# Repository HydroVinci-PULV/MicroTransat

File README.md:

# Architecture
Ceci est une ébauche de l'architecture finale des systèmes embarqués du bateau.

Cette présentation de l'architecture est amenée à évoluer en fonction des besoins du projet.

> **Note :** Les protocoles de communications entre les différents composants ne sont pas représentatifs de la réalité puisque le choix des composants n'est pas définitif à ce stade.

# Composants

## Ordinateur de bord

<p>Considérant que notre bateau autonomme puisse être apparenté à un drone, nous avons fait le choix d'utiliser un <i>flight controller</i> comme ordinateur de bord. C'est pourquoi nous utilisons au sein de notre architecture de navigation un <i>BeagleBone Blue</i> choisit pour sa compatibilité avec .</p>

Vous trouverez plus d'information sur le *BeagleBone Blue* sur [la page dédiée](../../wiki/BeagleBone-Blue) dans le wiki du projet.

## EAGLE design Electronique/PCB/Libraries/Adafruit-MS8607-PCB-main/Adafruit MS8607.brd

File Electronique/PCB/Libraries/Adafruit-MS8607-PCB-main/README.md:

## Adafruit MS8607 PTH Sensor PCB

<a href="http://www.adafruit.com/products/4716"><br/>
Click here to purchase one from the Adafruit shop</a>

PCB files for the Adafruit MS8607 PTH Sensor. 

Format is EagleCAD schematic and board layout
* https://www.adafruit.com/product/4716

### Description

Because of their many applications, Pressure, Temperature, and Humidity sensors (PHT sensors) are a common offering from semiconductor companies. The MS8607 PHT sensor from TE Connectivity  does an admirable job of measuring a wide range of all three environmental conditions. Each and every MS8607 sensor is calibrated at the factory and the calibration constants stored in the sensor itself. This sensor is a one stop shop for all your common weather and environmental related metrics. Just add a MS8607 and you’ll be ready to finish your enclosure and retire as a [Dubia Cockroach Farmer](https://dubiaroachdepot.com/guidance/breeding-dubia-roaches#thermometer)

The MS8607 provides the previously mentioned factory-calibrated pressure, temperature, and humidity data are recorded as **16-bit** values and made available over an I2C bus for simple, two wire (plus power and ground!) connection to your microcontroller. Pressure measurements accuracy comes in at **+/- 2 hPa**, relative humidity at **+/- 3% rH**, and temperature is good to within 1 degree Celsius. One standout feature of the MS8607 is it’s very respectable low power consumption at **as low as 0.78 µA** ! That’s hardly anything! Along with carefully managed microcontroller power usage, getting good battery life out of your sensing project will be that much easier.

### License

Adafruit invests time and resources providing this open source design, please support Adafruit and open-source hardware by purchasing products from [Adafruit](https://www.adafruit.com)!

Designed by Bryan Siepert for Adafruit Industries.

Creative Commons Attribution/Share-Alike, all text above must be included in any redistribution. 
See license.txt for additional details.

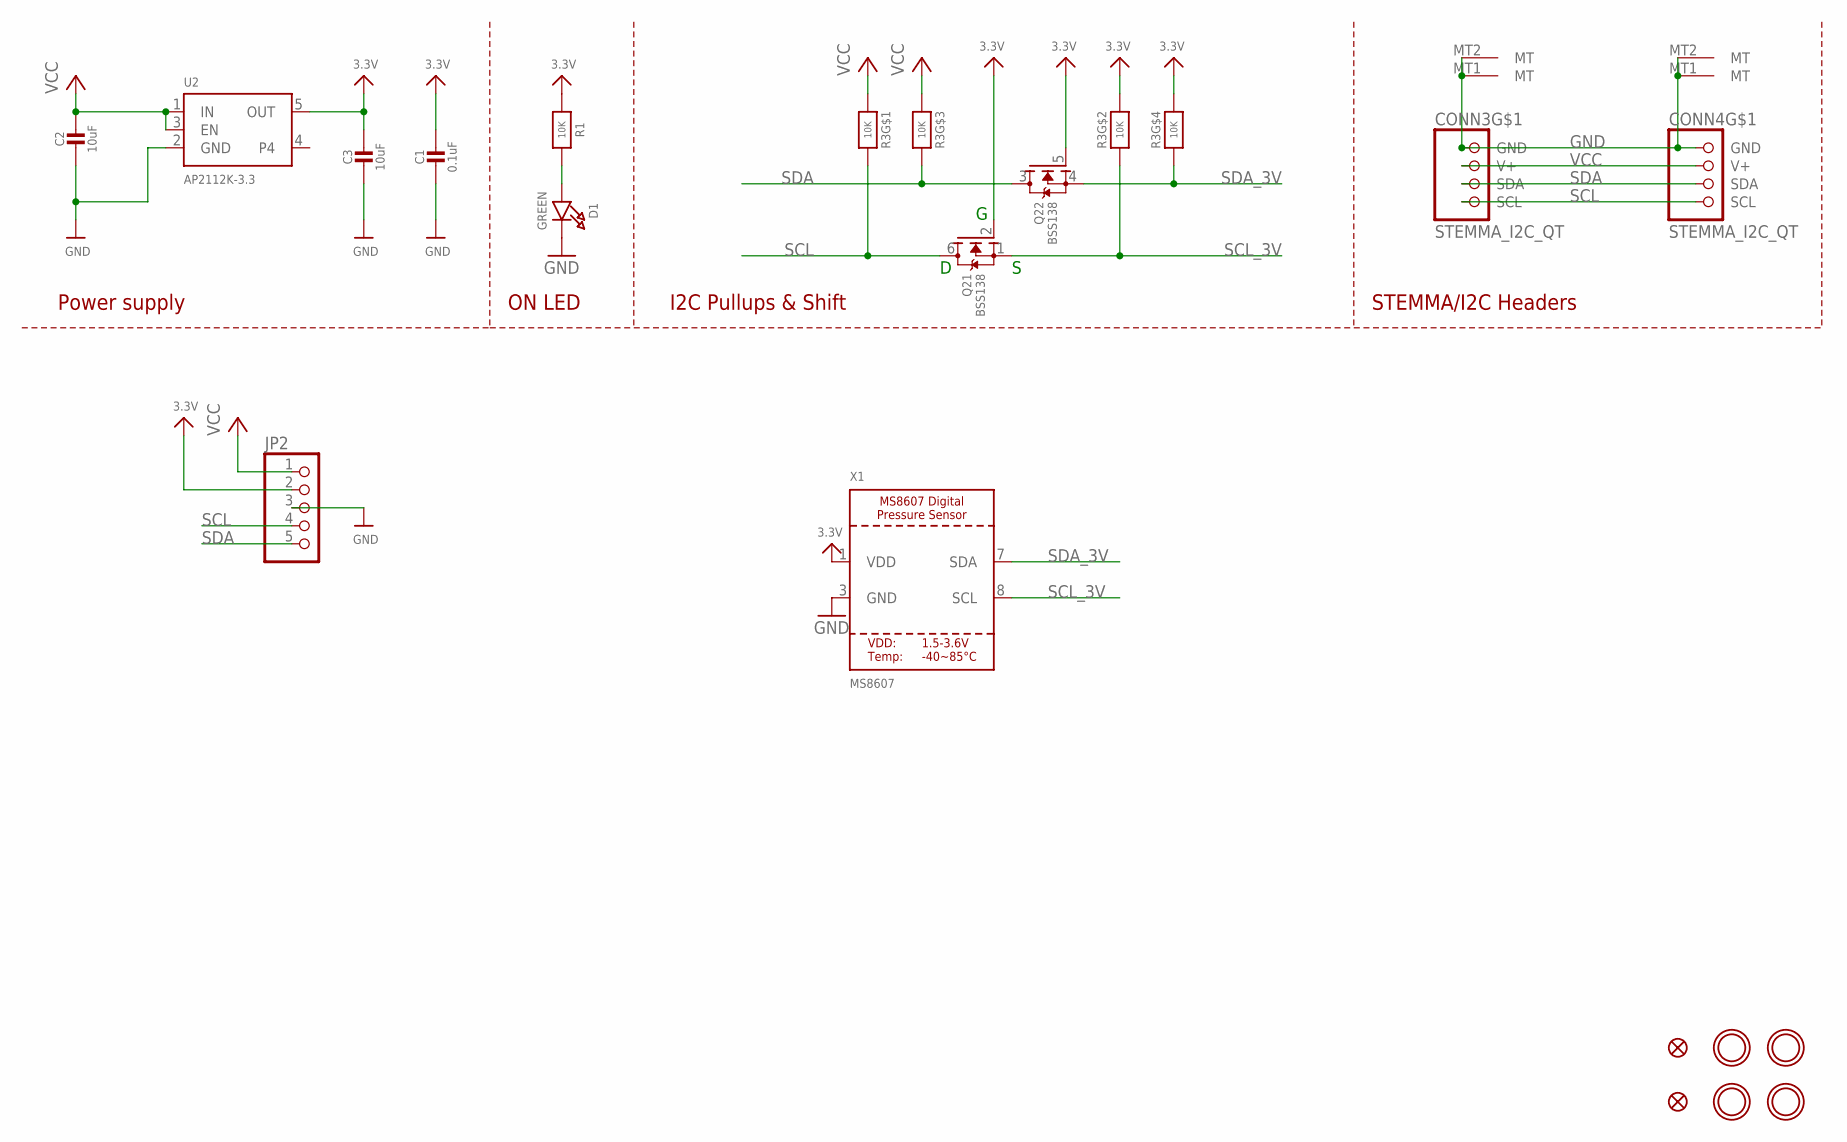
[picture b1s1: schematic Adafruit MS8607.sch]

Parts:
C1: 0.1uF; 0603-NO
C2, C3: 10uF; 0805-NO
CONN3, CONN4: STEMMA_I2C_QT; JST_SH4
D1: GREEN; CHIPLED_0603_NOOUTLINE
FID3, FID4: FIDUCIAL_1MM
JP2: HEADER-1X5ROUND; 1X05_ROUND
Q2: BSS138; SOT363
R1: 10K; 0603-NO
R3: 10K; RESPACK_4X0603
U2: AP2112K-3.3; SOT23-5
U$1, U$17, U$19, U$21: MOUNTINGHOLE2.5; MOUNTINGHOLE_2.5_PLATED
X1: MS8607

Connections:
3.3V: C1.1, C3.1, JP2.2, Q2.2 (G), Q2.5 (G), R1.1, R3.2 (1), R3.4 (1), U2.5 (OUT), X1.1 (VDD)
GND: C1.2, C2.2, C3.2, CONN3.1 (GND), CONN3.MT1 (MT), CONN3.MT2 (MT), CONN4.1 (GND), CONN4.MT1 (MT), CONN4.MT2 (MT), D1.C, JP2.3, U2.2 (GND), X1.3 (GND)
unnamed: D1.A, R1.2
SCL: CONN3.4 (SCL), CONN4.4 (SCL), JP2.4, Q2.6 (D), R3.8 (2)
SCL_3V: Q2.1 (S), R3.7 (2), X1.8 (SCL)
SDA: CONN3.3 (SDA), CONN4.3 (SDA), JP2.5, Q2.3 (D), R3.6 (2)
SDA_3V: Q2.4 (S), R3.5 (2), X1.7 (SDA)
VCC: C2.1, CONN3.2 (V+), CONN4.2 (V+), JP2.1, R3.1, R3.3 (1), U2.1 (IN), U2.3 (EN)

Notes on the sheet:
I2C Pullups & Shift
STEMMA/I2C Headers
ON LED
Power supply

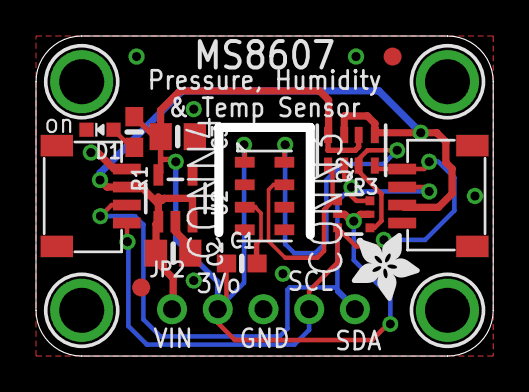
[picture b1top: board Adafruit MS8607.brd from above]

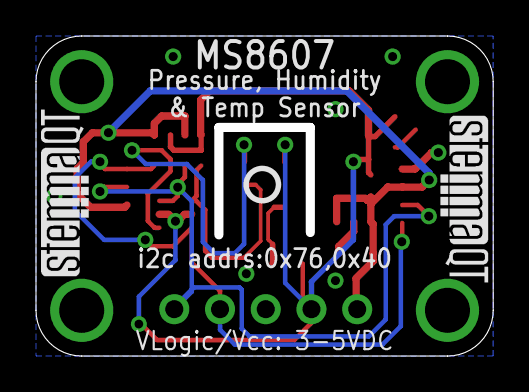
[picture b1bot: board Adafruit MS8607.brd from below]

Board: 2 copper layers, 25.4 x 17.8 mm, 22 parts (3 on the bottom side), 8 nets.

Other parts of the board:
U$22: ADAFRUIT_3.5MM
U$25: PCBFEAT-REV-040
U$30, U$31: STEMMAQT

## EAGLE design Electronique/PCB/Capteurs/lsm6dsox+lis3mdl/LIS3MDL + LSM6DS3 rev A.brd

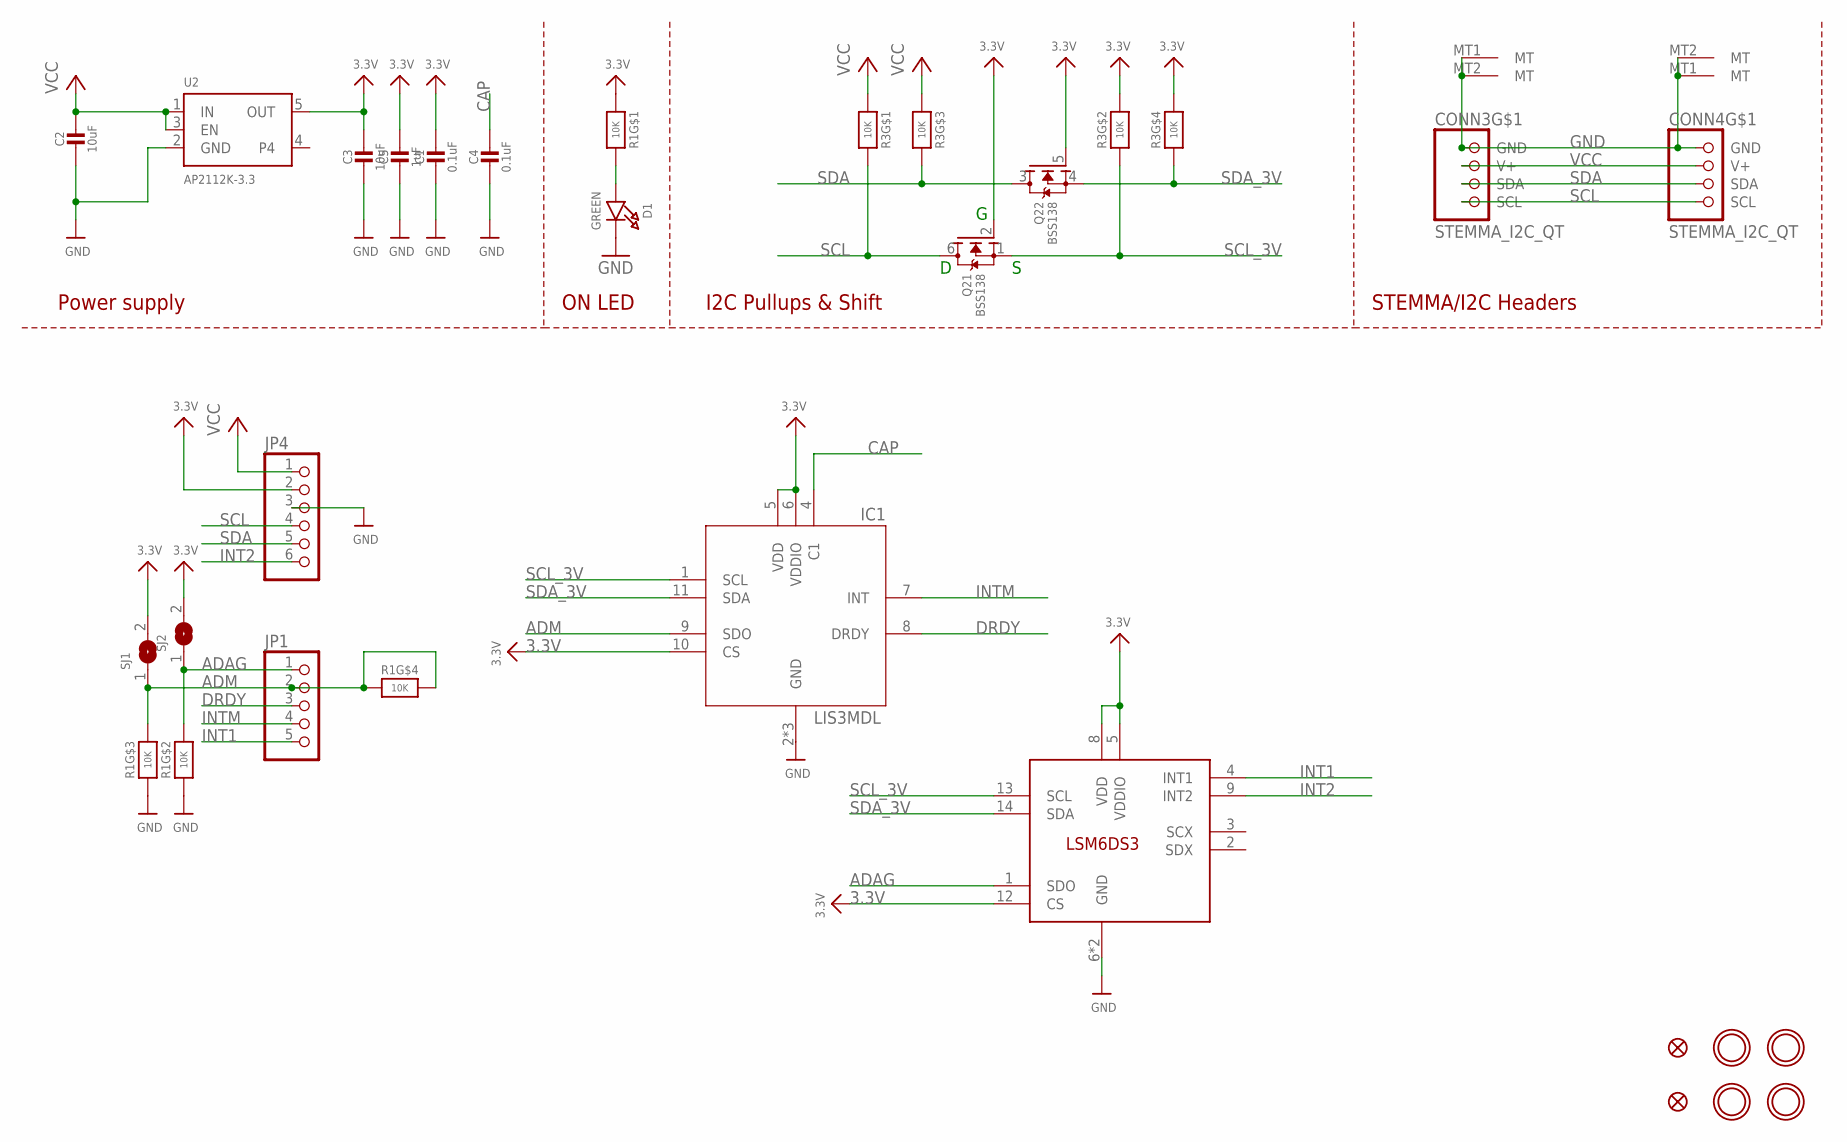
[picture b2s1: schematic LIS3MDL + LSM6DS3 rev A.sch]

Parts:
C1, C4: 0.1uF; 0603-NO
C2, C3: 10uF; 0805-NO
C5: 1uF; 0603-NO
CONN3, CONN4: STEMMA_I2C_QT; JST_SH4
D1: GREEN; CHIPLED_0603_NOOUTLINE
FID3, FID4: FIDUCIAL_1MM
IC1: LIS3MDL; LGA12_2X2MM
JP1: HEADER-1X570MIL; 1X05_ROUND_70
JP4: HEADER-1X670MIL; 1X06_ROUND_70
Q2: BSS138; SOT363
R1, R3: 10K; RESPACK_4X0603
SJ1, SJ2: SOLDERJUMPER; SOLDERJUMPER_ARROW_NOPASTE
U2: AP2112K-3.3; SOT23-5
U$1, U$17, U$19, U$21: MOUNTINGHOLE2.5; MOUNTINGHOLE_2.5_PLATED
U$36: LSM6DS3; LGA-14L

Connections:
3.3V: C1.1, C3.1, C5.1, IC1.5 (VDD), IC1.6 (VDDIO), IC1.10 (CS), JP4.2, Q2.2 (G), Q2.5 (G), R1.1, R3.2 (1), R3.4 (1), SJ1.2, SJ2.2, U2.5 (OUT), U$36.5 (VDDIO), U$36.8 (VDD), U$36.12 (CS)
ADAG: JP1.1, R1.7 (2), SJ2.1, U$36.1 (SDO)
ADM: IC1.9 (SDO), JP1.2, R1.4 (1), R1.5 (2), R1.6 (2), SJ1.1
CAP: C4.1, IC1.4 (C1)
DRDY: IC1.8 (DRDY), JP1.3
GND: C1.2, C2.2, C3.2, C4.2, C5.2, CONN3.1 (GND), CONN3.MT1 (MT), CONN3.MT2 (MT), CONN4.1 (GND), CONN4.MT1 (MT), CONN4.MT2 (MT), D1.C, IC1.2 (GND), IC1.3 (GND), IC1.12 (GND), JP4.3, R1.2 (1), R1.3 (1), U2.2 (GND), U$36.6 (GND), U$36.7 (GND)
INT1: JP1.5, U$36.4 (INT1)
INT2: JP4.6, U$36.9 (INT2)
INTM: IC1.7 (INT), JP1.4
unnamed: D1.A, R1.8 (2)
SCL: CONN3.4 (SCL), CONN4.4 (SCL), JP4.4, Q2.6 (D), R3.8 (2)
SCL_3V: IC1.1 (SCL), Q2.1 (S), R3.7 (2), U$36.13 (SCL)
SDA: CONN3.3 (SDA), CONN4.3 (SDA), JP4.5, Q2.3 (D), R3.6 (2)
SDA_3V: IC1.11 (SDA), Q2.4 (S), R3.5 (2), U$36.14 (SDA)
VCC: C2.1, CONN3.2 (V+), CONN4.2 (V+), JP4.1, R3.1, R3.3 (1), U2.1 (IN), U2.3 (EN)

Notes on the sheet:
I2C Pullups & Shift
STEMMA/I2C Headers
ON LED
Power supply

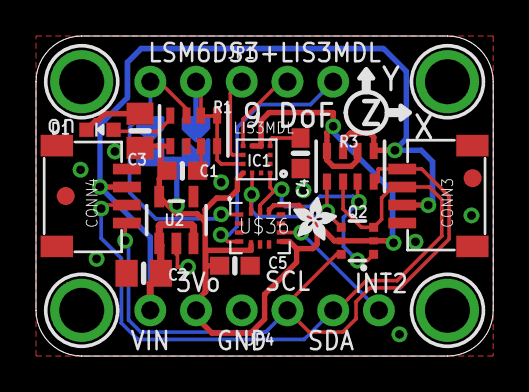
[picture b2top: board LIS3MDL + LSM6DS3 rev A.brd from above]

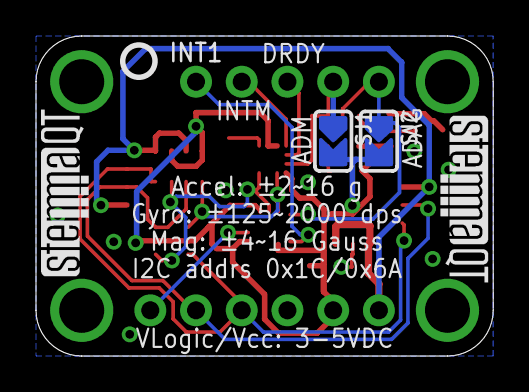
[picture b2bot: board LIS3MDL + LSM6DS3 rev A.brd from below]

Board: 2 copper layers, 25.4 x 17.8 mm, 28 parts (5 on the bottom side), 15 nets.

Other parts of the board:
U$20: ADAFRUIT_2.5MM
U$25: PCBFEAT-REV-040
U$30, U$31: STEMMAQT

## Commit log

2021-12-15 navigation algorithms research
2022-01-16 compressor
2022-01-16 Modélisations ordinateur de bord
2022-01-17 Modélisation bateau
2022-01-17 décompressor
2022-01-18 compatibilité solidworks
2022-01-18 autres modé
2022-02-04 decompress : ok pour lat
2022-02-04 data to send
2022-02-05 gps done + unit tests + explications
2022-02-05 debug instructions
2022-02-05 start boat speed compression
2022-02-05 boat speed + data concat
2022-02-05 clean
2022-02-05 updated instruction with unit test
2022-02-05 bits
2022-02-21 logos
2022-02-24 update banner
2022-03-08 Update telemetry.c
    added compression and decompression for heading
2022-04-06 Add architecture v3 to readme
2022-04-06 add paraph on flight controller
2022-04-06 fix wiki page url
2022-04-19 start rust conversion
2022-04-19 Create LICENSE
2022-04-22 j'enleve la v3
2022-04-22 mise a jour archi
2022-05-30 genetic algo for navigation
2022-06-08 bug correction in concat + added unit tests
2022-06-08 bug correction + added unit tests
2022-07-17 draft of rs485 pcb
2022-08-23 BBB pinout
2023-02-01 cad files for adafruit temp/hum/pres sensor + imu
2023-02-02 pcb files for sensors
2023-03-09 update to pcb for environnement sensors + external libs
2023-03-22 kicad schematic for ttl to rs485 conversion module
2023-03-26 ttl to rs485 proto pcb
2023-03-26 update to ttl to rs485 pcb
2023-04-01 pcb updates
2026-04-14 Bump rand from 0.8.5 to 0.9.3 in /Télémetrie
    Bumps [rand](https://github.com/rust-random/rand) from 0.8.5 to 0.9.3.
    - [Release notes](https://github.com/rust-random/rand/releases)
    - [Changelog](https://github.com/rust-random/rand/blob/0.9.3/CHANGELOG.md)
    - [Commits](https://github.com/rust-random/rand/compare/0.8.5...0.9.3)
    ---
    updated-dependencies:
2026-04-22 Bump rand from 0.8.5 to 0.8.6 in /Télémetrie
    Bumps [rand](https://github.com/rust-random/rand) from 0.8.5 to 0.8.6.
    - [Release notes](https://github.com/rust-random/rand/releases)
    - [Changelog](https://github.com/rust-random/rand/blob/0.8.6/CHANGELOG.md)
    - [Commits](https://github.com/rust-random/rand/compare/0.8.5...0.8.6)
    ---
    updated-dependencies:

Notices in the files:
parts and their libraries:
microbuilder: This work is placed in the public domain, and may be freely used for commercial and non-commercial work with the following conditions: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
